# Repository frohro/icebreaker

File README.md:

# iCEBreaker FPGA

This repository is to update the Bitsy 1.1c so it has JLCPCB part numbers and can be ordered.

The iCEBreaker FPGA board is a low cost, open-source educational FPGA
development board.

The main motivating application of this board is for classes and workshops
teaching the use of the open source FPGA design flow using
[Yosys](http://www.clifford.at/yosys/),
[nextpnr](https://github.com/YosysHQ/nextpnr),
[icestorm](http://www.clifford.at/icestorm/),
[iverilog](http://iverilog.icarus.com/),
[symbiflow](https://github.com/SymbiFlow) and others. This means the board has
to be low cost and have a nice set of features to allow for the design of
interesting classes and workshop exercises. At the same time we want to allow
the user to use the proprietary vendor tools if they choose to. Because of that
we need to be compatible with their firmware upload tools.

## iCEBreaker Hardware Specifications

* iCE40UP5K in QFN48 (SG48) package
  * [iCE40 UltraPlus 5K](http://www.latticesemi.com/-/media/LatticeSemi/Documents/DataSheets/iCE/iCE40-UltraPlus-Family-Data-Sheet.ashx)
  * 5280 Logic Cells (4-LUT + Carry + FF)
  * 128 KBit Dual-Port Block RAM
  * 1 MBit (128 KB) Single-Port RAM
  * PLL, Two SPI and two I2C hard IPs
  * Two internal oscillators (10 kHz and 48 MHz)
  * 8 DSPs (16x16 multiply + 32 bit accumulate)
  * 3x 24mA drive and 3x hard PWM IP

* QSPI-DDR-capable flash 128 MBit (16 MB)
  * We selected to use the Winbond
    [W25Q128JVSIM](http://www.winbond.com/resource-files/w25q128jv_dtr%20revc%2003272018%20plus.pdf)
  * We want to enable projects that access the flash and we want to provide the
    highest flash access speed possible.

* [FT2232H](http://www.ftdichip.com/Support/Documents/DataSheets/ICs/DS_FT2232H.pdf) interface (microUSB plug)
  * programming compatible with iCEstick and HX8K board
    * works with [Dimond Programmer](http://www.latticesemi.com/programmer) and
      [iceprog](https://github.com/cliffordwolf/icestorm/tree/master/iceprog)
  * serial port compatible with iCEstick and HX8K breakout board
  * 12 MHz XTAL oscillator (shared with FPGA)
  * Solder jumpers to offer direct SRAM programming (like on HX8K breakout board)

* 39 I/O capable pins:
  * 4 pins for config (SDI, SDO, SCK, CSB)
    * Either loading config from on board FLASH chip or provided through the
      FTDI chip with direct SRAM config.
  * 2 extra GPIO pins for QSPI
    * Together with the config pins, allows storage of additional data in the
      FLASH chip, and high speed QSPI DDR access. For example
      [picosoc](https://github.com/cliffordwolf/picorv32/tree/master/picosoc)
      firmware.
  * 3 PINs for RGB LED (pin header)
  * 2 LEDs (one on output-only PLL pin)
  * 1 Clock pin (on PLL GBIN)
  * 1 UART Rx Pin via FTDI
  * 1 UART Tx Pin via FTDI
  * 1 Push Button
  * 16 PINs on dual PMOD
  * 8 PINs on single PMOD / snap-off section

* Support for FTDI Async FIFO mode
  * We want to support FTDI Async mode via some (unpopulated by default) zero
    ohm resistors
  * This shares 8 GPIOs with the single PMOD / snap-off section
  * This would also enable use of full list of RS232 signals
  * BDATA[0] -- Tx on FTDI / Rx on FPGA (always connected, no zohm resistor
    required)
  * BDATA[1] -- Rx on FTDI / Tx on FPGA (always connected, no zohm resistor
    required)
  * BDATA[7:2] -- Shared with snap-off section (via zohm resistor footprint)
  * RX Full -- Shared with snap-off section (via zohm resistor footprint)
  * TX Empty -- Shared with snap-off section (via zohm resistor footprint)
  * Read -- Shared with LED 1 (via zohm resistor footprint, LED used as RX
    indicator)
  * Write -- Shared with LED 2 (via zohm resistor footprint, LED used as TX
    indicator)
  * WakeUp -- Shared with Push Button (via zohm resistor footprint)
  * This configuration uses the following pins when the jumpers ore reconfigured:
    * The two on board red and green LED pins
    * The on board user button pin
    * snap off section single PMOD pins 

* Snap-off section (convertible to PMOD host / PMOD device)
  * 5 LEDs in similar arrangement to iCEstick
  * 3 Push Buttons

* Other stuff
  * Status LEDs for Power and CDONE (Configuration DONE)
  * Header with supply rails: 5V, 3V3, 1V2, GND
  * Debug header for all 6 QSPI pins
  * Test points for UART Rx / Tx signals
  * Jumpers or zohm resistors on all rails for measuring currents
  * Four 3mm mounting holes on the main section and two more on the snap-off
    section
  * The two LEDs on the main section should be wired "active low" so they work 
    well as indicator LEDs for FIFO read/write.
  * The five LEDs on the snap-off section should be wired "active high"
  * A zohm resistor for Bank 2 supply so that the IO voltage can be changed. Use
    Bank 2 for one of the ports on the double PMOD.
  * There should be auxilary 5V pin headers available for the PMODs. Some PMOD
    need either higher voltage or need to regulate their own voltage from 5V.

* Unpopulated parts shipped with the board
  * 3x Host PMOD (2x for dual PMOD port, 1x for snap-off section)
  * 1x Device PMOD (for other side of snap-off section)

**iCEBreaker block diagram**  

**iCEBreaker V1.0b pinout legend**  

**iCEBreaker V1.0b jumper legend**  

## iCEBreaker Bitsy

iCEBreaker Bitsy is the smaller but just-as-capable sibling to iCEBreaker. At just 36x18mm, it is compatible with the Teensy form-factor and can be easily embedded into any project.

* iCE40UP5K in QFN48 (SG48) package
  * PLL, two SPI and two I2C hard IPs
* 128M (16MiB) DDR- and QPI-capable Flash Memory
* 64M (8MiB) QPI-capable Pseudo-SRAM
* USB-C interface (comes preloaded with a [RISC-V soft-core USB bootloader](//github.com/no2fpga/no2bootloader))
* RGB LED connected to 3x 24mA hard PWM IP pins
* Two user LEDs (one shared with RAM-CS)
* Status LED for CDONE (Configuration DONE)
* 12MHz external clock (on PLL GBIN)
* One user button
* Supply rails: 3.3V and 1.2V
* FPGA SPI/programming header
  * 4 pins for config (SDI, SDO, SCK, CS)
  * 2 extra GPIO pins for QSPI/QPI
  * CDONE (Configuration DONE), CRESET (Configuration RESET), 3.3V, and GND
* Teensy form-factor compatible
* Compatible with Feather ecosystem using a [Teensy 3.x Feather Adapter](//adafruit.com/product/3200)
* Castellated edges and single-side-load for easy module integration

## Branding

[iCEbreaker](https://twitter.com/AboveVacant/status/948323920595308545)

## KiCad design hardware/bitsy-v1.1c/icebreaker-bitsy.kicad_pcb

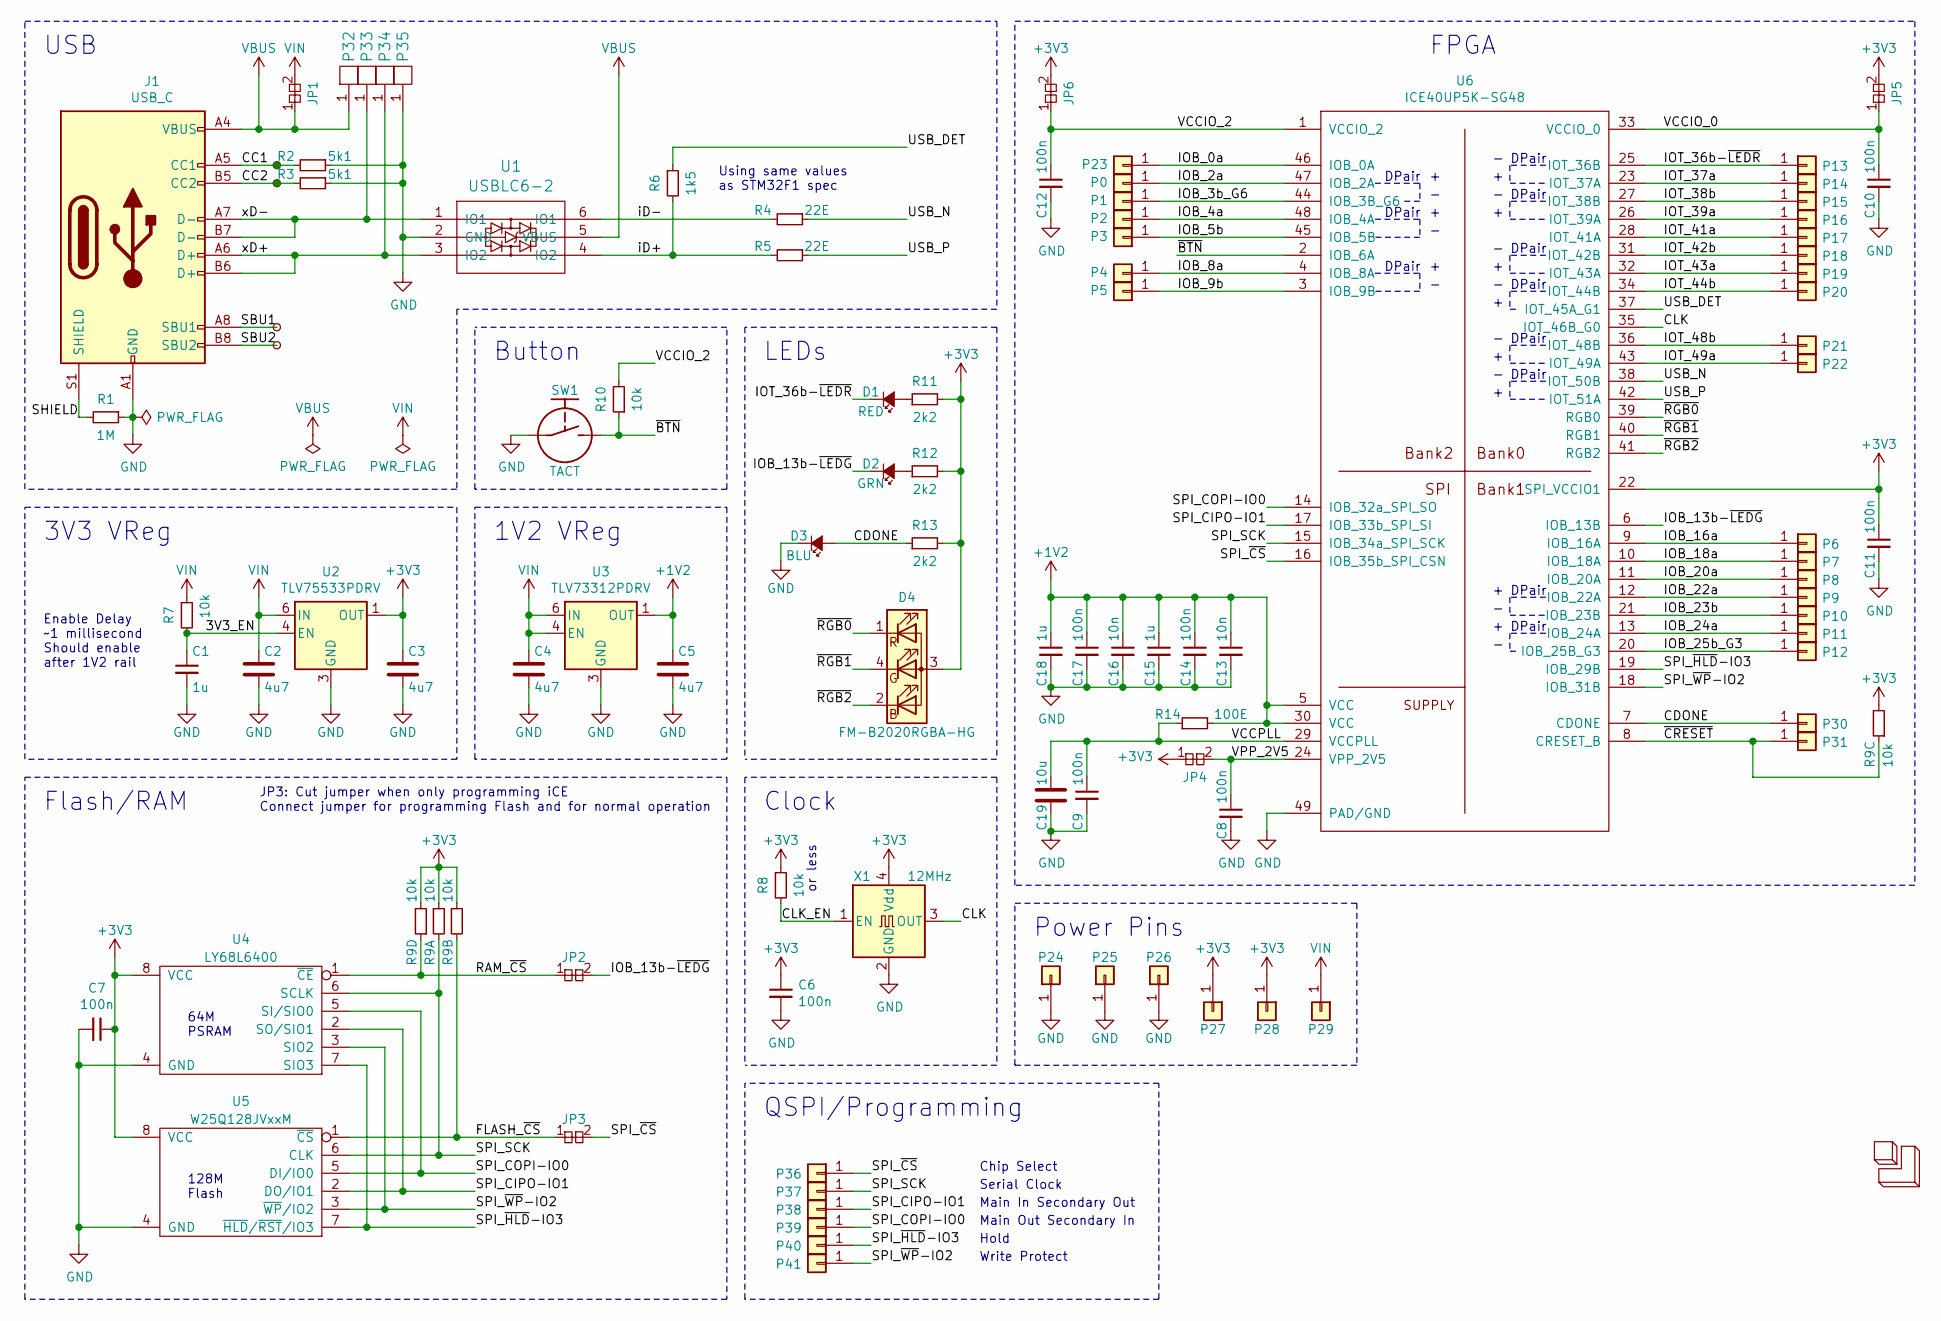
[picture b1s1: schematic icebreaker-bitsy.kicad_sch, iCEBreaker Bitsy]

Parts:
C1, C15, C18: 1u; C_0402; LCSC C52923
C2, C3, C4, C5: 4u7; C_0603
C6, C7, C8, C9, C10, C14, C17: 100n; C_0402; LCSC C1525
C11: 100n; C_0402
C12: 100n; C_0402_1005Metric; LCSC C1525
C13, C16: 10n; C_0402; LCSC C15195
C19: 10u; C_0603; LCSC C19702
D1: RED; D_0603; LCSC C2286
D2: GRN; D_0603; LCSC C19171392
D3: BLU; D_0603; LCSC C19171394
D4: FM-B2020RGBA-HG; LED_TRI_2020; LCSC C42421005
J1: USB_C; USB_C_Receptacle_HRO_TYPE-C-31-M-12; LCSC C2765186
JP1: VIN-VBUS; J_NC_0603_40
JP2: RAM_CS-LEDG; J_NC_0402_15
JP3: Flash_CS-SPI_CS; J_NC_0402_15
JP4: Vpp2v5; J_NC_0402_30
JP5: VccIO0; J_NC_0603_30
JP6: VccIO2; J_NC_0603_30
LOGO1: 1BitSquared; 1b2_Logo_SilkS_2mm
P0: 0; Pin_Header_Straight_Round_1x01_Castellated
P1: 1; Pin_Header_Straight_Round_1x01_Castellated
P2: 2; Pin_Header_Straight_Round_1x01_Castellated
P3: 3; Pin_Header_Straight_Round_1x01_Castellated
P4: 4; Pin_Header_Straight_Round_1x01_Castellated
P5: 5; Pin_Header_Straight_Round_1x01_Castellated
P6: 6; Pin_Header_Straight_Round_1x01_Castellated
P7: 7; Pin_Header_Straight_Round_1x01_Castellated
P8: 8; Pin_Header_Straight_Round_1x01_Castellated
P9: 9; Pin_Header_Straight_Round_1x01_Castellated
P10: 10; Pin_Header_Straight_Round_1x01_Castellated
P11: 11; Pin_Header_Straight_Round_1x01_Castellated
P12: 12; Pin_Header_Straight_Round_1x01_Castellated
P13: 13; Pin_Header_Straight_Round_1x01_Castellated
P14: 14; Pin_Header_Straight_Round_1x01_Castellated
P15: 15; Pin_Header_Straight_Round_1x01_Castellated
P16: 16; Pin_Header_Straight_Round_1x01_Castellated
P17: 17; Pin_Header_Straight_Round_1x01_Castellated
P18: 18; Pin_Header_Straight_Round_1x01_Castellated
P19: 19; Pin_Header_Straight_Round_1x01_Castellated
P20: 20; Pin_Header_Straight_Round_1x01_Castellated
P21: 21; Pin_Header_Straight_Round_1x01_Castellated
P22: 22; Pin_Header_Straight_Round_1x01_Castellated
P23: 23; Pin_Header_Straight_Round_1x01_Castellated
P24, P25, P26: GND; Pin_Header_Straight_Round_1x01_Castellated
P27, P28: 3V3; Pin_Header_Straight_Round_1x01_Castellated
P29: VIN; Pin_Header_Straight_Round_1x01_Castellated
P30: CDONE; Pin_Header_Straight_Round_1x01_Castellated
P31: CRESET; Pin_Header_Straight_Round_1x01_Castellated
P32, P33, P34, P35: UP; PAD_SMD_1x2.65_ROUNDED
P36: CS; Pin_Header_Straight_Round_1x01
P37: SCK; Pin_Header_Straight_Round_1x01
P38: CIPO; Pin_Header_Straight_Round_1x01
P39: COPI; Pin_Header_Straight_Round_1x01
P40: IO3; PAD_SMD_R_1x1
P41: IO2; PAD_SMD_R_1x1
R1: 1M; R_0402; LCSC C26083
R2, R3: 5k1; R_0402; LCSC C25905
R4: 22E; R_0402; LCSC C25092
R5: 22E; R_0402_1005Metric; LCSC C25092
R6: 1k5; R_0402; LCSC C25867
R7, R8, R10: 10k; R_0402; LCSC C25744
R9: 10k; R_Array_Convex_4x0402; LCSC C326872
R11: 2k2; R_0402; LCSC C25879
R12, R13: 2k2; R_0402_1005Metric; LCSC C25879
R14: 100E; R_0402; LCSC C25076
SW1: TACT; TS-1088-AR02016; LCSC C720477
TP1: CC1; TestPoint_Pad_D0.75mm
TP2: CC2; TestPoint_Pad_D0.75mm
TP3: SBU1; TestPoint_Pad_D0.75mm
TP4: SBU2; TestPoint_Pad_D0.75mm
U1: USBLC6-2; SOT-666; LCSC C7519
U2: TLV75533PDRV; WSON-6-1EP_2x2mm_P0.65mm_EP1x1.6mm; LCSC C2861750
U3: TLV73312PDRV; WSON-6-1EP_2x2mm_P0.65mm_EP1x1.6mm; LCSC C2863369
U4: LY68L6400; SOIC-8_3.9x4.9mm_P1.27mm; LCSC C261881
U5: W25Q128JVxxM; WSON-8-1EP_6x5mm_P1.27mm_EP3.4x4.3mm; LCSC C2441427
U6: ICE40UP5K-SG48; QFN-48-1EP_7x7mm_Pitch0.5mm
X1: 12MHz; Oscillator_SMD_SCTF_S2DXX-4Pin_2.5x2.0mm; LCSC C9002

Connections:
+1V2: C5.1, C13.1, C14.1, C15.1, C16.1, C17.1, C18.1, R14.2, U3.1 (OUT), U6.5 (VCC), U6.30 (VCC)
+3V3: C3.1, C6.1, C7.1, C11.1, D4.3 (A), JP4.1, JP5.2, JP6.2, P27.1, P28.1, R8.1, R9.1, R9.3, R9.6, R9.8, R11.2, R12.2, R13.2, U2.1 (OUT), U4.8 (VCC), U5.8 (VCC), U6.22 (SPI_VCCIO1), X1.4 (Vdd)
/3V3_EN: C1.1, R7.2, U2.4 (EN)
/CC1: J1.A5 (CC1), R2.2, TP1.1
/CC2: J1.B5 (CC2), R3.2, TP2.1
/CDONE: D3.A, P30.1, R13.1, U6.7 (CDONE)
/CLK: U6.35 (IOT_46B_G0), X1.3 (OUT)
/CLK_EN: R8.2, X1.1 (EN)
/FLASH_~CS: JP3.1, R9.4, U5.1 (~CS)
/IOB_0a: P23.1, U6.46 (IOB_0A)
/IOB_2a: P0.1, U6.47 (IOB_2A)
/IOB_3b_G6: P1.1, U6.44 (IOB_3B_G6)
/IOB_4a: P2.1, U6.48 (IOB_4A)
/IOB_5b: P3.1, U6.45 (IOB_5B)
/IOB_8a: P4.1, U6.4 (IOB_8A)
/IOB_9b: P5.1, U6.3 (IOB_9B)
/IOB_13b-~LEDG: D2.C, JP2.2, U6.6 (IOB_13B)
/IOB_16a: P6.1, U6.9 (IOB_16A)
/IOB_18a: P7.1, U6.10 (IOB_18A)
/IOB_20a: P8.1, U6.11 (IOB_20A)
/IOB_22a: P9.1, U6.12 (IOB_22A)
/IOB_23b: P10.1, U6.21 (IOB_23B)
/IOB_24a: P11.1, U6.13 (IOB_24A)
/IOB_25b_G3: P12.1, U6.20 (IOB_25B_G3)
/IOT_36b-~LEDR: D1.C, P13.1, U6.25 (IOT_36B)
/IOT_37a: P14.1, U6.23 (IOT_37A)
/IOT_38b: P15.1, U6.27 (IOT_38B)
/IOT_39a: P16.1, U6.26 (IOT_39A)
/IOT_41a: P17.1, U6.28 (IOT_41A)
/IOT_42b: P18.1, U6.31 (IOT_42B)
/IOT_43a: P19.1, U6.32 (IOT_43A)
/IOT_44b: P20.1, U6.34 (IOT_44B)
/IOT_48b: P21.1, U6.36 (IOT_48B)
/IOT_49a: P22.1, U6.43 (IOT_49A)
/RAM_~CS: JP2.1, R9.7, U4.1 (~CE)
/SBU1: J1.A8 (SBU1), TP3.1
/SBU2: J1.B8 (SBU2), TP4.1
/SHIELD: J1.S1 (SHIELD), R1.2
/SPI_CIPO-IO1: P38.1, U4.2 (SO/SIO1), U5.2 (DO/IO1), U6.17 (IOB_33b_SPI_SI)
/SPI_COPI-IO0: P39.1, U4.5 (SI/SIO0), U5.5 (DI/IO0), U6.14 (IOB_32a_SPI_SO)
/SPI_SCK: P37.1, R9.2, U4.6 (SCLK), U5.6 (CLK), U6.15 (IOB_34a_SPI_SCK)
/SPI_~CS: JP3.2, P36.1, U6.16 (IOB_35b_SPI_CSN)
/SPI_~HLD-IO3: P40.1, U4.7 (SIO3), U5.7 (~HLD/~RST/IO3), U6.19 (IOB_29B)
/SPI_~WP-IO2: P41.1, U4.3 (SIO2), U5.3 (~WP/IO2), U6.18 (IOB_31B)
/USB_DET: R6.1, U6.37 (IOT_45A_G1)
/USB_N: R4.1, U6.38 (IOT_50B)
/USB_P: R5.1, U6.42 (IOT_51A)
/VCCIO_0: C10.1, JP5.1, U6.33 (VCCIO_0)
/VCCIO_2: C12.1, JP6.1, R10.2, U6.1 (VCCIO_2)
/VCCPLL: C9.1, C19.1, R14.1, U6.29 (VCCPLL)
/VPP_2V5: C8.1, JP4.2, U6.24 (VPP_2V5)
/iD+: R5.2, R6.2, U1.4 (IO2)
/iD-: R4.2, U1.6 (IO1)
/xD+: J1.A6 (D+), J1.B6 (D+), P34.1 (PAD), U1.3 (IO2)
/xD-: J1.A7 (D-), J1.B7 (D-), P33.1 (PAD), U1.1 (IO1)
/~BTN: R10.1, SW1.2, U6.2 (IOB_6A)
/~CRESET: P31.1, R9.5, U6.8 (CRESET_B)
/~RGB0: D4.1 (RK), U6.39 (RGB0)
/~RGB1: D4.4 (GK), U6.40 (RGB1)
/~RGB2: D4.2 (BK), U6.41 (RGB2)
GND: C1.2, C2.2, C3.2, C4.2, C5.2, C6.2, C7.2, C8.2, C9.2, C10.2, C11.2, C12.2, C13.2, C14.2, C15.2, C16.2, C17.2, C18.2, C19.2, D3.C, J1.A1 (GND), J1.A12 (GND), J1.B1 (GND), J1.B12 (GND), P24.1, P25.1, P26.1, P35.1 (PAD), R1.1, R2.1, R3.1, SW1.1, U1.2 (GND), U2.3 (GND), U2.7 (GND), U3.3 (GND), U3.7 (GND), U4.4 (GND), U5.4 (GND), U6.49 (PAD/GND), X1.2 (GND)
unnamed: D1.A, R11.1
unnamed: D2.A, R12.1
VBUS: J1.A4 (VBUS), J1.A9 (VBUS), J1.B4 (VBUS), J1.B9 (VBUS), JP1.1, P32.1 (PAD), U1.5 (VBUS)
VIN: C2.1, C4.1, JP1.2, P29.1, R7.1, U2.6 (IN), U3.4 (EN), U3.6 (IN)

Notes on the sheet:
DPair
1V2 VReg
Using same values as STM32F1 spec
Clock
Main Out Secondary In
Main In Secondary Out
QSPI/Programming
or less
Power Pins
Chip Select
Write Protect
JP3: Cut jumper when only programming iCE Connect jumper for programming Flash and for normal operation
USB
LEDs
Enable Delay ~1 millisecond Should enable after 1V2 rail
64M PSRAM
Hold
128M Flash
3V3 VReg
FPGA
Button
Flash/RAM
Serial Clock

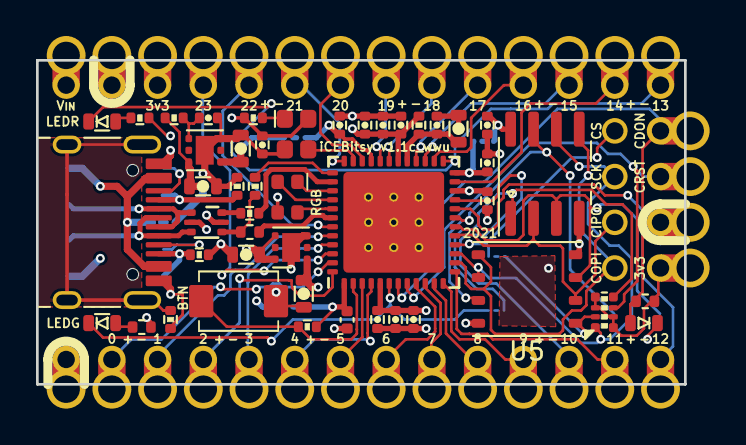
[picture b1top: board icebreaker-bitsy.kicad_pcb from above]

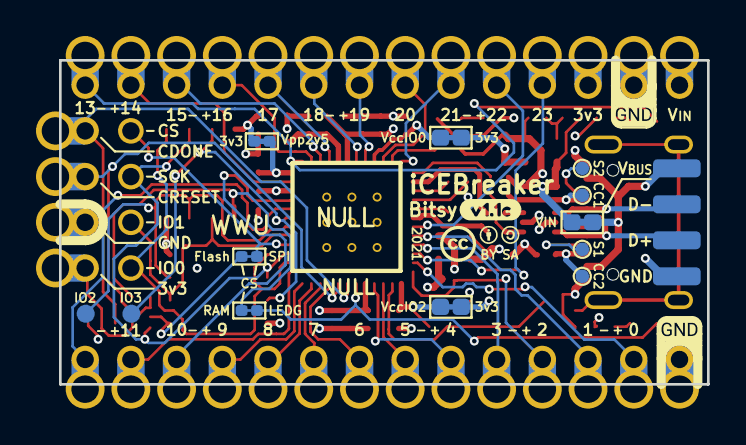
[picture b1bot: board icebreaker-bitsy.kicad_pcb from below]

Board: 4 copper layers, 36.0 x 18.0 mm, 101 parts (19 on the bottom side), 65 nets.

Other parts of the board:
svg2mod, svg2mod#2, svg2mod#3: G***; svg2mod

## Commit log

2025-06-11 Adding JLCPCB
2025-06-11 changed some 0402 to use the regular library in Kicad v9
2025-06-12 PCB changes for JLCPCB parts made.
2025-06-12 Added 3D models
2025-06-12 Fixed silkscreen
2025-06-12 Update readme with purpose
2025-06-16 Fixed footprint of U5, etc.
2025-06-18 Added some footprints

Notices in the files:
hardware/bitsy-v1.1c/icebreaker-bitsy.kicad_pcb:
© 2018-2021 1BitSquared
© 2018-2020 Piotr Esden-Tempski
© 2020-2021 Jordi Pakey-Rodriguez
License: CC BY-SA 4.0
